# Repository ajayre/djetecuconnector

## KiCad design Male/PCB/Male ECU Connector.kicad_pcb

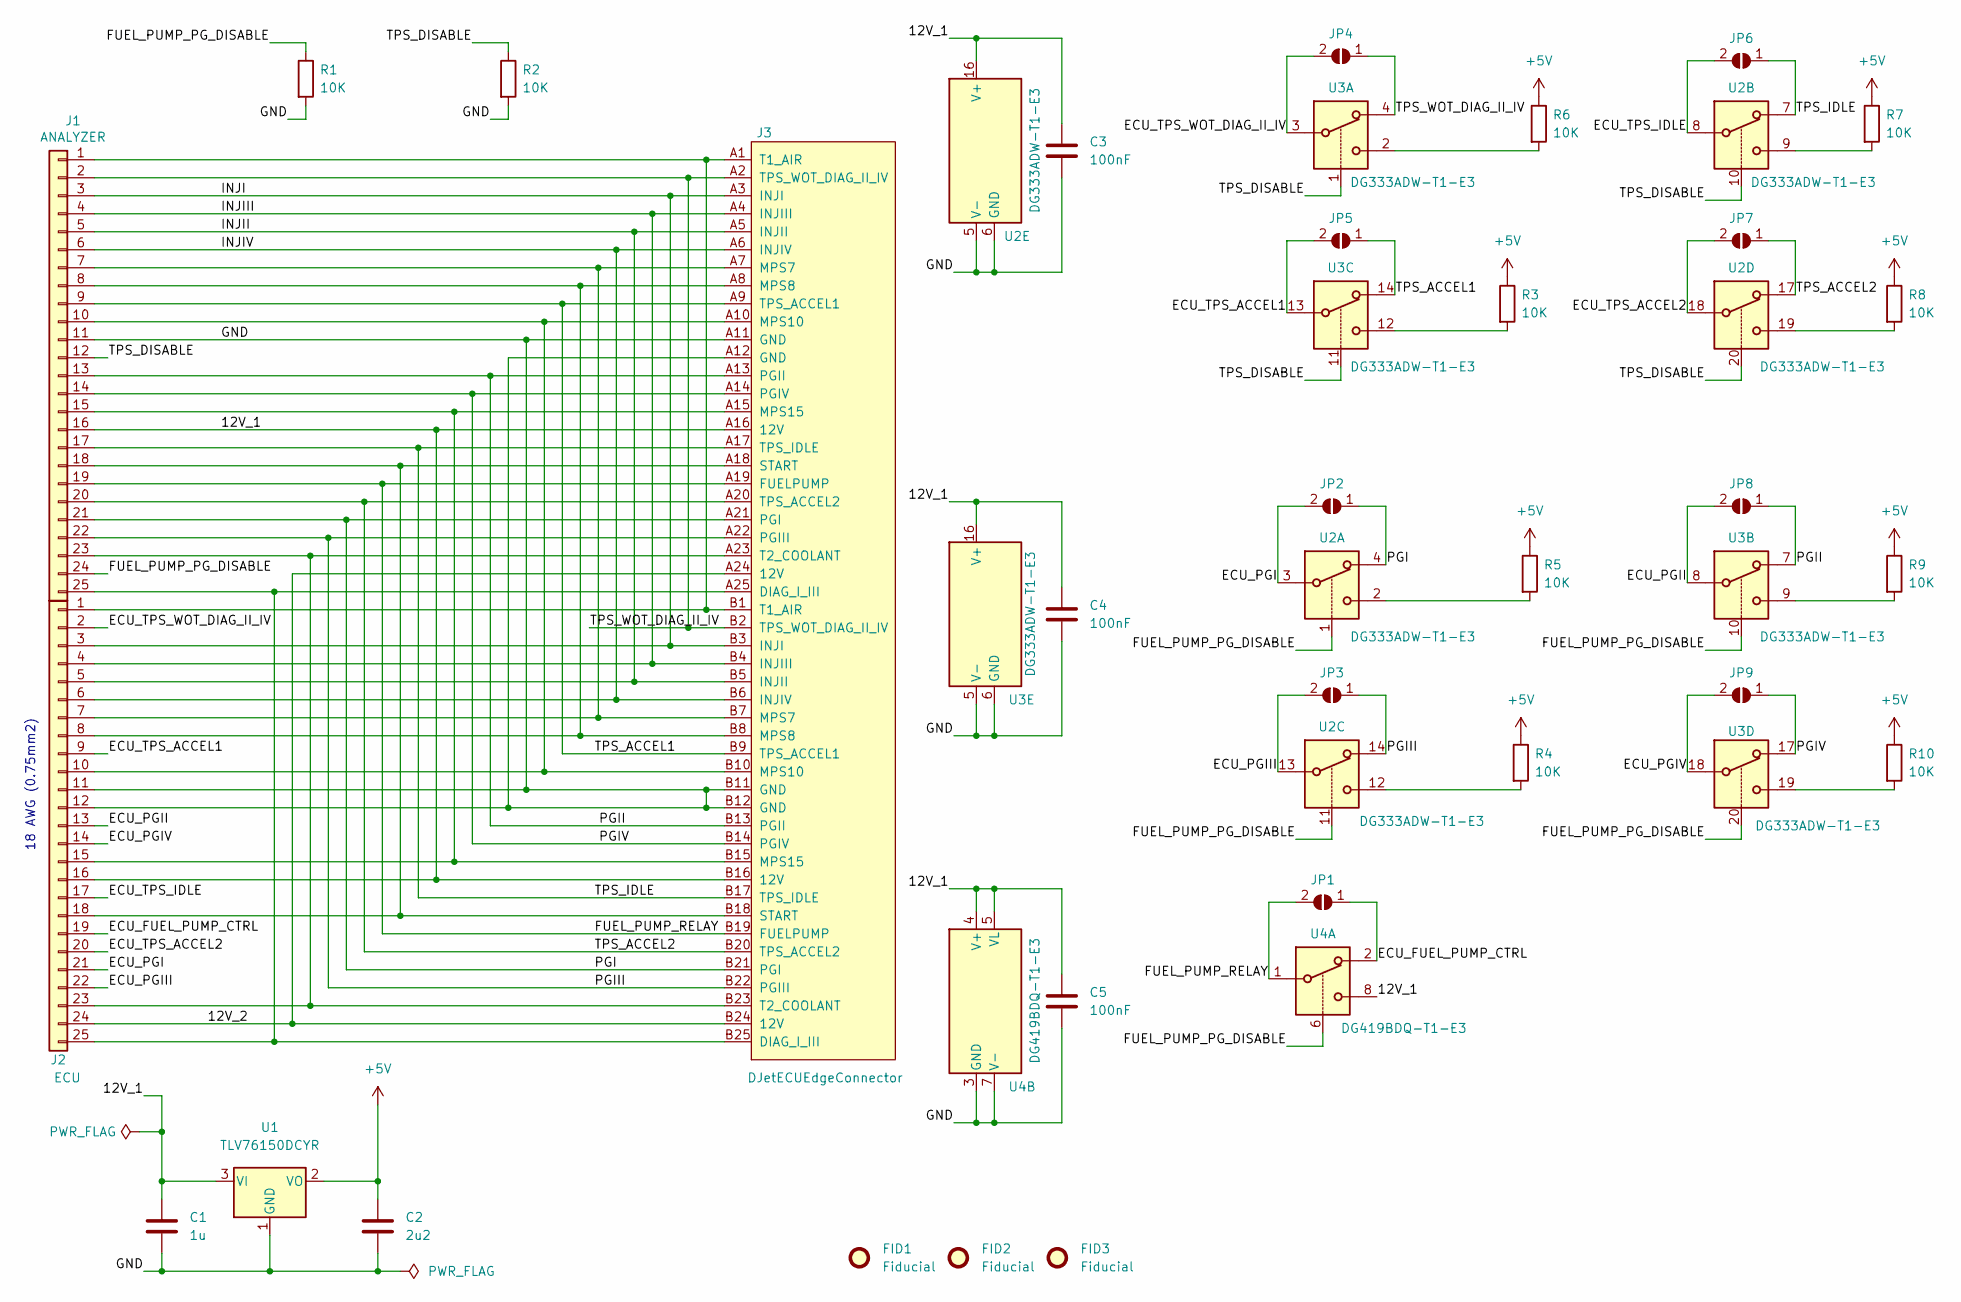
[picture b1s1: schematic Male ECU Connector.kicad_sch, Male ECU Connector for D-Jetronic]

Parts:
C1: 1u; C_0603_1608Metric
C2: 2u2; C_0603_1608Metric
C3, C4, C5: 100nF; C_0603_1608Metric
FID1, FID2, FID3: Fiducial; Fiducial_0.5mm_Mask1.5mm
J1: ANALYZER; DSUB-25_Female_Horizontal_P2.77x2.84mm_EdgePinOffset7.70mm_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
J2: ECU; Pins_1x25_P3.00mm_18AWG
J3: DJetECUEdgeConnector; D-Jetronic ECU Edge Connector
JP1, JP2, JP3, JP4, JP5, JP6, JP7, JP8, JP9: NO_ANALYZER; SolderJumper-2_P1.3mm_Open_TrianglePad1.0x1.5mm
R1, R2, R3, R4, R5, R6, R7, R8, R9, R10: 10K; R_0603_1608Metric
U1: TLV76150DCYR; SOT-223-3_TabPin2
U2, U3: DG333ADW-T1-E3; SOIC-20W_7.5x12.8mm_P1.27mm
U4: DG419BDQ-T1-E3; MSOP-8_3x3mm_P0.65mm

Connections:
+5V: C2.1, R3.1, R4.1, R5.1, R6.1, R7.1, R8.1, R9.1, R10.1, U1.2 (VO)
/12V_1: C1.1, C3.1, C4.1, C5.1, J1.16, J2.16, J3.A16 (12V), J3.B16 (12V), U1.3 (VI), U2.16 (V+), U3.16 (V+), U4.4 (V+), U4.5 (VL), U4.8
/12V_2: J2.24, J3.A24 (12V), J3.B24 (12V)
/ECU_FUEL_PUMP_CTRL: J2.19, JP1.1 (A), U4.2
/ECU_PGI: J2.21, JP2.2 (B), U2.3
/ECU_PGII: J2.13, JP8.2 (B), U3.8
/ECU_PGIII: J2.22, JP3.2 (B), U2.13
/ECU_PGIV: J2.14, JP9.2 (B), U3.18
/ECU_TPS_ACCEL1: J2.9, JP5.2 (B), U3.13
/ECU_TPS_ACCEL2: J2.20, JP7.2 (B), U2.18
/ECU_TPS_IDLE: J2.17, JP6.2 (B), U2.8
/ECU_TPS_WOT_DIAG_II_IV: J2.2, JP4.2 (B), U3.3
/FUEL_PUMP_PG_DISABLE: J1.24, R1.1, U2.1, U2.11, U3.10, U3.20, U4.6
/FUEL_PUMP_RELAY: J1.19, J3.A19 (FUELPUMP), J3.B19 (FUELPUMP), JP1.2 (B), U4.1
/GND: C1.2, C2.2, C3.2, C4.2, C5.2, J1.11, J2.11, J2.12, J3.A11 (GND), J3.A12 (GND), J3.B11 (GND), J3.B12 (GND), R1.2, R2.2, U1.1 (GND), U2.5 (V-), U2.6 (GND), U3.5 (V-), U3.6 (GND), U4.3 (GND), U4.7 (V-)
/INJI: J1.3, J2.3, J3.A3 (INJI), J3.B3 (INJI)
/INJII: J1.5, J2.5, J3.A5 (INJII), J3.B5 (INJII)
/INJIII: J1.4, J2.4, J3.A4 (INJIII), J3.B4 (INJIII)
/INJIV: J1.6, J2.6, J3.A6 (INJIV), J3.B6 (INJIV)
/PGI: J1.21, J3.A21 (PGI), J3.B21 (PGI), JP2.1 (A), U2.4
/PGII: J1.13, J3.A13 (PGII), J3.B13 (PGII), JP8.1 (A), U3.7
/PGIII: J1.22, J3.A22 (PGIII), J3.B22 (PGIII), JP3.1 (A), U2.14
/PGIV: J1.14, J3.A14 (PGIV), J3.B14 (PGIV), JP9.1 (A), U3.17
/TPS_ACCEL1: J1.9, J3.A9 (TPS_ACCEL1), J3.B9 (TPS_ACCEL1), JP5.1 (A), U3.14
/TPS_ACCEL2: J1.20, J3.A20 (TPS_ACCEL2), J3.B20 (TPS_ACCEL2), JP7.1 (A), U2.17
/TPS_DISABLE: J1.12, R2.1, U2.10, U2.20, U3.1, U3.11
/TPS_IDLE: J1.17, J3.A17 (TPS_IDLE), J3.B17 (TPS_IDLE), JP6.1 (A), U2.7
/TPS_WOT_DIAG_II_IV: J1.2, J3.A2 (TPS_WOT_DIAG_II_IV), J3.B2 (TPS_WOT_DIAG_II_IV), JP4.1 (A), U3.4
unnamed: J1.1, J2.1, J3.A1 (T1_AIR), J3.B1 (T1_AIR)
unnamed: J1.7, J2.7, J3.A7 (MPS7), J3.B7 (MPS7)
unnamed: J1.8, J2.8, J3.A8 (MPS8), J3.B8 (MPS8)
unnamed: J1.10, J2.10, J3.A10 (MPS10), J3.B10 (MPS10)
unnamed: J1.15, J2.15, J3.A15 (MPS15), J3.B15 (MPS15)
unnamed: J1.18, J2.18, J3.A18 (START), J3.B18 (START)
unnamed: J1.23, J2.23, J3.A23 (T2_COOLANT), J3.B23 (T2_COOLANT)
unnamed: J1.25, J2.25, J3.A25 (DIAG_I_III), J3.B25 (DIAG_I_III)
unnamed: R3.2, U3.12
unnamed: R4.2, U2.12
unnamed: R5.2, U2.2
unnamed: R6.2, U3.2
unnamed: R7.2, U2.9
unnamed: R8.2, U2.19
unnamed: R9.2, U3.9
unnamed: R10.2, U3.19

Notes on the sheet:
18 AWG (0.75mm2)

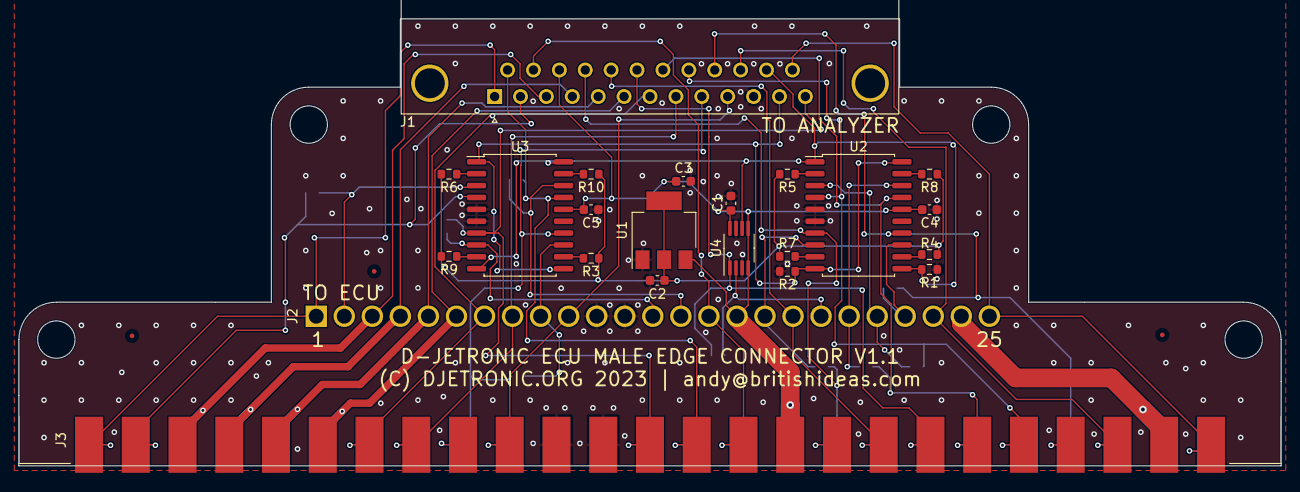
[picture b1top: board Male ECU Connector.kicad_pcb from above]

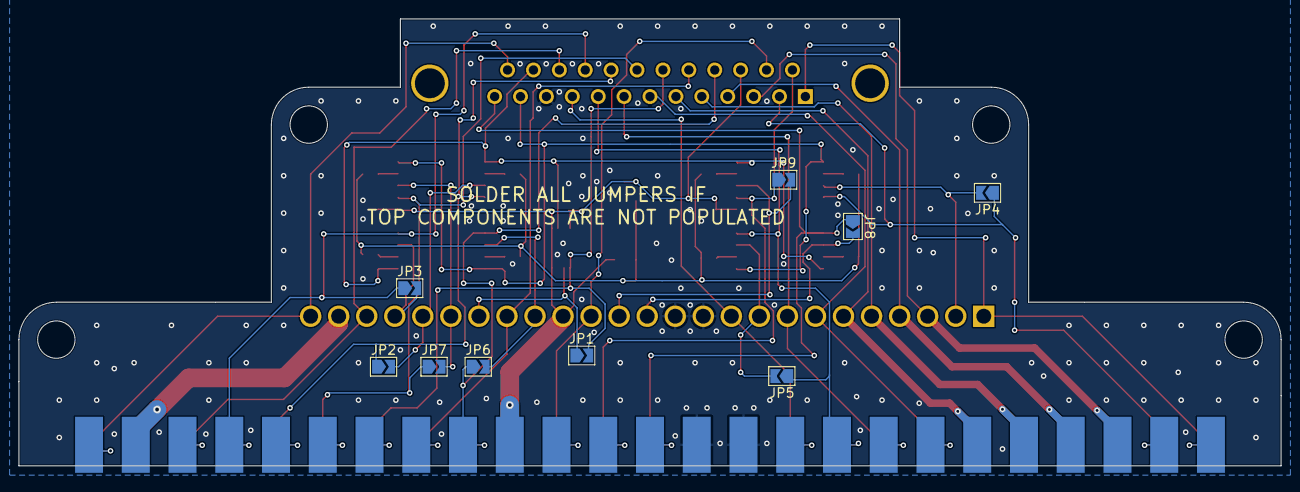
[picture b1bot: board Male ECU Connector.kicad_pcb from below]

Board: 2 copper layers, 135.0 x 47.8 mm, 34 parts (9 on the bottom side), 44 nets.

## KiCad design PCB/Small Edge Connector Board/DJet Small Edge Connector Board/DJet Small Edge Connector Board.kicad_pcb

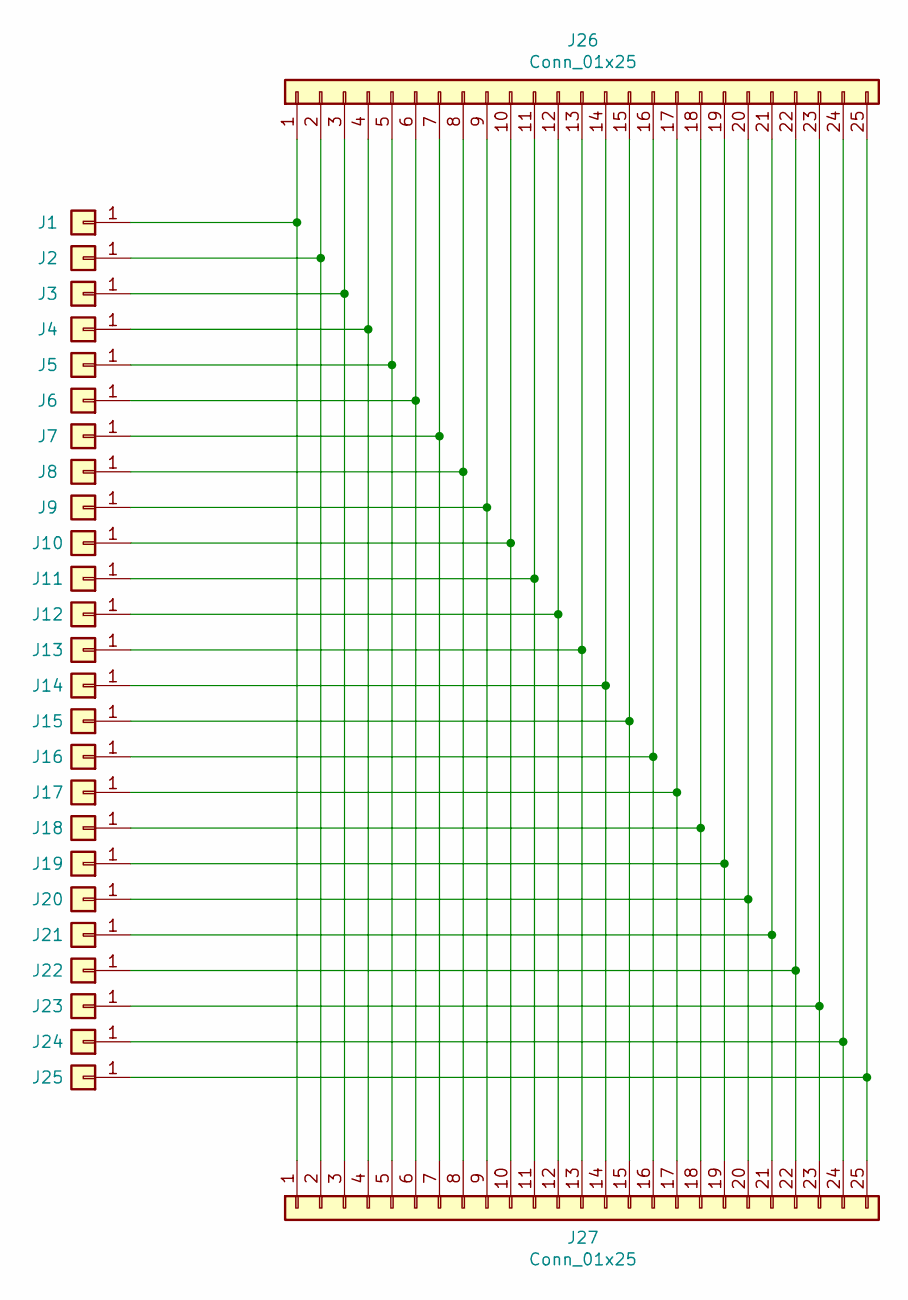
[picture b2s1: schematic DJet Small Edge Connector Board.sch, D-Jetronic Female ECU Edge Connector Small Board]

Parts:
J1, J2, J3, J4, J5, J6, J7, J8, J9, J10, J11, J12, J13, J14, J15, J16, J17, J18, J19, J20, J21, J22, J23, J24, J25: Conn_01x01; TE-1871059-1
J26, J27: Conn_01x25; PinHeader_1x25_P2.54mm_Vertical

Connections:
unnamed: J1.1, J26.1, J27.1
unnamed: J2.1, J26.2, J27.2
unnamed: J10.1, J26.10, J27.10
unnamed: J11.1, J26.11, J27.11
unnamed: J12.1, J26.12, J27.12
unnamed: J13.1, J26.13, J27.13
unnamed: J14.1, J26.14, J27.14
unnamed: J15.1, J26.15, J27.15
unnamed: J16.1, J26.16, J27.16
unnamed: J17.1, J26.17, J27.17
unnamed: J18.1, J26.18, J27.18
unnamed: J19.1, J26.19, J27.19
unnamed: J20.1, J26.20, J27.20
unnamed: J21.1, J26.21, J27.21
unnamed: J22.1, J26.22, J27.22
unnamed: J23.1, J26.23, J27.23
unnamed: J24.1, J26.24, J27.24
unnamed: J25.1, J26.25, J27.25
unnamed: J3.1, J26.3, J27.3
unnamed: J4.1, J26.4, J27.4
unnamed: J5.1, J26.5, J27.5
unnamed: J6.1, J26.6, J27.6
unnamed: J7.1, J26.7, J27.7
unnamed: J8.1, J26.8, J27.8
unnamed: J9.1, J26.9, J27.9

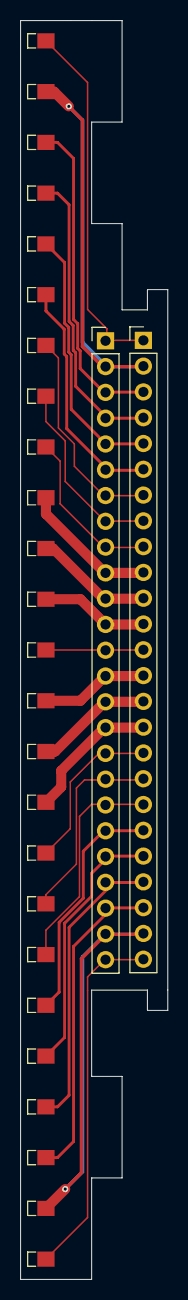
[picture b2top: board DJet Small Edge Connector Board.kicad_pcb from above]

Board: 2 copper layers, 14.5 x 124.0 mm, 27 parts (0 on the bottom side), 25 nets.

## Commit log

2022-05-01 Started work on connector idea.
2022-05-03 Added small edge connector board for use in female ECU connector.
2022-05-03 Working on CAD model.
2022-05-03 Reorg.
2022-05-03 Added CAD model of PCB.
2022-05-03 Updated CAD model and removed unused files.
2022-05-04 Working on case.
2022-05-04 WIP.
2022-05-15 Work in progress.
2022-12-28 Working on updated design.
2023-10-07 3D printed connector.
2023-10-07 Renamed folder
2023-10-07 Added male connector. Added original female connector.
2023-10-20 Added male connector PCB
2023-10-20 Moved CAD files.
2023-10-21 Converted project to KiCAD 6.
2023-10-21 Added relay to disable fuel pump.
2023-10-21 Added larger holes for 18AWG (0.75mm2) engine harness wires. Rounded back corners of PCB to make it easier to design case. Added solder jumper to make relay optional.
2023-11-05 Laid out PCB fpr male connector.
2023-11-11 Completed PCB design for male connector.
2023-11-20 Changed analyzer connector to DB25.
2023-11-20 Added CAD model.
2023-11-20 Added gold fingers to CAD model.
2023-11-27 Added additional mounting holes and reduced PCB size. Added first version of housing.
2024-01-10 Final female housing with and without a handle.
